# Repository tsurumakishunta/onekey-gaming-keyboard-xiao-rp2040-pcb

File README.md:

# OneKey Gaming Keyboard PCB for XIAO RP2040

[日本語](#日本語) | [English](#english)

## 日本語

### 概要

Seeed Studio XIAO RP2040とPCBマウント式の5ピンMXスイッチを上下に重ねる、1キーUSBゲーミングキーボード専用のKiCad基板設計です。

上側のキャリア基板をXIAO RP2040と同じ位置に重ね、XIAOに搭載されているRGB LEDの光軸をMXスイッチの光窓へ合わせます。キャリア基板に外付けLEDは搭載せず、XIAOの内蔵RGB LEDを利用します。

本プロジェクトでは基板の製造と実装まで行っています。ただし、部品メーカーや製造ロットによる寸法差があるため、再製造するときは後述の注意事項を確認し、最初に少数で試作してください。

### 専用ファームウェア

この基板は、次のファームウェアリポジトリと組み合わせて使用できます。

**[onekey-gaming-keyboard-xiao-rp2040](https://github.com/tsurumakishunta/onekey-gaming-keyboard-xiao-rp2040)**

専用ファームウェアを書き込むと、次のように動作します。

- MXスイッチを1回押すと、USBキーボード入力として `arigatou` を1回送信します。
- 日本語IMEがローマ字入力になっている場合、通常は「ありがとう」と入力されます。
- Enterキーは送信しません。
- XIAO RP2040の内蔵RGB LEDが、7色の滑らかなグラデーションで光り続けます。

この基板だけではUSBキーボードとして動作しません。XIAO RP2040へのファームウェア書き込みが必要です。

### 基板の構造

- 下側：部品面を上にしたSeeed Studio XIAO RP2040
- 上側：MXスイッチを取り付ける積層キャリア基板
- XIAO側：1列7ピンのメスソケットを2本
- キャリア基板側：1列7ピンのオスヘッダーを2本
- スイッチ：PCBマウント式の標準5ピンMX互換スイッチ
- USB-C端子：XIAO RP2040の端子をそのまま使用

不透明な下部ハウジングのMXスイッチでは、XIAOのRGB LEDの光がキーへ届きません。RGB対応の透明または半透明ハウジングを持つスイッチと、光を通すキーキャップを使用してください。

この設計はホットスワップソケットには対応しておらず、手はんだを前提としています。MX Low Profile、Kailh Choc、光学式、磁気式スイッチ用の基板ではありません。

### 回路

回路は、MXスイッチをXIAO RP2040のD0とGNDの間に接続するシンプルな構成です。

```text
XIAO pin 1  D0 / GPIO26 ---- SW1 pad 1
XIAO pin 13 GND ----------- SW1 pad 2
```

ファームウェアがXIAOの内部プルアップ抵抗を有効にするため、キャリア基板上に外付け抵抗、ダイオード、コンデンサー、LEDはありません。

ヘッダー穴とMXスイッチの接点穴はスルーホールメッキされています。MXスイッチの中央・左右の固定穴と、面付け基板のミシン目は非メッキ穴です。

### 単体基板の仕様

| 項目 | 仕様 |
|---|---:|
| リビジョン | Rev.B |
| 外形寸法 | 21.10 × 17.80 mm |
| 層数 | 2層 |
| 基板厚 | 1.00 mm |
| 材質 | FR-4 |
| 銅厚 | 1 oz想定 |
| 角 | R1.00 mm |
| MXスイッチ | PCBマウント式5ピン、1U |
| スイッチ入力 | D0 / GPIO26、押下時GND |

基板厚は、積層高さとMXスイッチの固定形状を考慮して **1.00 mm** を前提にしています。1.60 mmへ変更する場合は、ヘッダーのかみ合わせ、MXスイッチの固定爪、端子の突出量、XIAO上の部品との干渉を改めて確認してください。

### 4×5面付け基板

JLCPCBなどへまとめて発注できるように、単体基板を20枚配置したミシン目付きパネルを収録しています。

| 項目 | 仕様 |
|---|---:|
| 配列 | 4列 × 5行 |
| 取得できる単体基板 | 20枚 |
| パネル外形 | 98.40 × 95.40 mm |
| 単体基板ピッチ | 22.70 × 19.40 mm |
| ルーター溝 | 1.60 mm |
| 左右レール | 3.00 mm |
| タブ幅 | 5.00 mm |
| ミシン目 | 1列につき5穴、穴径0.60 mm、ピッチ0.95 mm |

部品を付けた状態で基板を折ると、スイッチ、ヘッダー、はんだ部へ大きな力がかかります。必ず基板を切り離し、端面を整えてから部品を実装してください。

### JLCPCB向け製造データ

アップロード用Gerber ZIPは次の場所にあります。

[`fabrication/onekey_revb_4x5_panel_JLCPCB.zip`](fabrication/onekey_revb_4x5_panel_JLCPCB.zip)

```text
SHA-256: E2092C8DA0B966CC4B055C34EE1AFF2BCEEBEC182B71E3D3F318ED53CC495E65
```

主な想定設定は次のとおりです。

- 2層、FR-4、1.00 mm、1 oz
- 面付け済み／Customer Panel
- 異なるデザイン数：1
- 4列 × 5行
- JLCPCBによる自動面付け：なし
- Vカット：なし
- PCBA：なし（自分ではんだ付け）

発注画面の名称や料金条件は変更される場合があります。アップロード後に検出寸法が **98.40 × 95.40 mm**、層数が2層であることを確認し、Gerberビューアで20枚すべての外形、光学ノッチ、配線、スルーホール、ミシン目を確認してください。面付けやルーター加工による追加料金が発生する可能性もあります。

### 組み立て時の注意

1. 4×5パネルを単体基板へ切り離し、ミシン目の端面を整えます。
2. キャリア基板の下面へオスヘッダーを取り付け、上面側ではんだ付けします。
3. 上面に残る端子がMXスイッチへ干渉しないよう、必要に応じて安全に処理します。
4. XIAO RP2040の部品面へメスソケットを取り付けます。
5. ヘッダーの向き、USB-C側、RGB LEDとMX光窓の位置を確認してからMXスイッチをはんだ付けします。
6. 導通と短絡がないことを確認してからXIAOを接続します。
7. 専用ファームウェアを書き込み、最初は空のテキストエディターで動作を確認します。

USBへ接続する前に、D0とGNDの短絡、隣接ヘッダーピン間のはんだブリッジ、XIAO上の部品とMX端子の接触がないことをテスターで確認してください。

### 検証と制限事項

- KiCad 10のERC：違反0件
- 単体基板のKiCad 10 DRC：違反0件、未接続0件
- 4×5パネルのKiCad 10 DRC：違反0件、未接続0件
- Gerber ZIP：銅箔2層、ソルダーマスク2層、シルク2層、外形、PTH・NPTHドリルを収録

ERCとDRCは、設計へ登録された電気的・二次元的な製造ルールを検査するものです。コネクターの実際の挿入深さ、基板間の高さ、MXスイッチ端子とXIAO部品のクリアランス、RGB光軸、キーキャップ、3Dプリントケースとの組み合わせまでは保証しません。使用する部品の現物で確認してください。

### KiCadで開く

KiCad 10以降で、次のプロジェクトファイルを開きます。

- 単体基板：[`hardware/revb_stacked/onekey_stacked_rev_b.kicad_pro`](hardware/revb_stacked/onekey_stacked_rev_b.kicad_pro)
- 4×5面付け：[`hardware/revb_panel/onekey_revb_4x5_panel.kicad_pro`](hardware/revb_panel/onekey_revb_4x5_panel.kicad_pro)

プロジェクト固有のシンボルとフットプリントは各ディレクトリの `libraries/` に含まれ、ライブラリテーブルは `${KIPRJMOD}` を使用した相対パスになっています。

### ファイル構成

```text
.
├── hardware/
│   ├── revb_stacked/       単体基板の回路図・PCB・プロジェクト内ライブラリ
│   └── revb_panel/         4×5面付けPCB・プロジェクト内ライブラリ
├── fabrication/            JLCPCBアップロード用Gerber ZIPとSHA-256
├── docs/images/            KiCadで生成した説明用レンダー
├── LICENSES/               第三者ライセンス
├── THIRD_PARTY_NOTICES.md  第三者データの出典と変更内容
├── LICENSE                 本プロジェクト独自部分のライセンス
└── README.md
```

### ライセンス

本プロジェクト独自部分はMIT Licenseです。プロジェクト内シンボルとフットプリントには、Seeed StudioおよびKiCad公式ライブラリを基に変更した部分が含まれます。詳細は [`THIRD_PARTY_NOTICES.md`](THIRD_PARTY_NOTICES.md) と `LICENSES/` を参照してください。

---

## English

### Overview

This repository contains the KiCad design files for a dedicated one-key USB gaming keyboard PCB. A PCB-mount five-pin MX switch is stacked directly above a standard Seeed Studio XIAO RP2040. The optical opening of the switch is aligned with the XIAO onboard addressable RGB LED, so no external LED is fitted to the carrier PCB.

The project has reached physical PCB fabrication and hand assembly. Component dimensions can still vary by manufacturer and production lot, so verify the actual switch, headers, sockets, keycap, and enclosure before ordering more than a small prototype quantity.

### Firmware

Use this PCB with the dedicated firmware repository:

**[onekey-gaming-keyboard-xiao-rp2040](https://github.com/tsurumakishunta/onekey-gaming-keyboard-xiao-rp2040)**

The firmware types `arigatou` once per press, does not send Enter, and continuously animates the XIAO onboard RGB LED through a smooth seven-color gradient. With a Japanese IME in romaji mode, the typed text will usually appear as `ありがとう`. The PCB does not operate as a USB keyboard until firmware has been installed on the XIAO RP2040.

### Electrical design

```text
XIAO pin 1  D0 / GPIO26 ---- SW1 pad 1
XIAO pin 13 GND ----------- SW1 pad 2
```

The firmware enables the internal pull-up. The carrier has no external resistor, diode, capacitor, or LED.

### Board specifications

- Single carrier: 21.10 × 17.80 mm, two-layer FR-4, 1.00 mm finished thickness
- Switch: PCB-mount five-pin 1U MX-compatible switch with a translucent RGB-capable lower housing
- Panel: 4 × 5 array, 20 boards, 98.40 × 95.40 mm
- Routed gaps: 1.60 mm; side rails: 3.00 mm; breakaway tabs: 5.00 mm
- Mouse bites: five 0.60 mm NPTH holes per row at 0.95 mm pitch
- Assembly: hand soldering after depanelization; hot-swap sockets are not supported

### JLCPCB fabrication package

The upload-ready Gerber archive is [`fabrication/onekey_revb_4x5_panel_JLCPCB.zip`](fabrication/onekey_revb_4x5_panel_JLCPCB.zip).

```text
SHA-256: E2092C8DA0B966CC4B055C34EE1AFF2BCEEBEC182B71E3D3F318ED53CC495E65
```

The intended baseline is a two-layer, 1.00 mm FR-4, 1 oz, customer-panelized PCB with one identical design arranged in four columns and five rows. Do not request automatic panelization, V-cuts, or PCBA. Verify the detected 98.40 × 95.40 mm dimensions and inspect every layer and drill file in the online Gerber viewer before ordering. Service labels, capabilities, and prices may change.

### Validation and limitations

KiCad 10 ERC and DRC pass with zero violations for the single-board project, and panel DRC passes with zero violations and zero unconnected pads. These checks validate only the encoded electrical and two-dimensional manufacturing rules. They do not guarantee connector insertion depth, board-to-board height, clearance to XIAO components, the optical path through a particular MX switch, keycap fit, or enclosure fit. Verify those items with the exact physical parts you intend to use.

Open the single-board project at [`hardware/revb_stacked/onekey_stacked_rev_b.kicad_pro`](hardware/revb_stacked/onekey_stacked_rev_b.kicad_pro) or the panel project at [`hardware/revb_panel/onekey_revb_4x5_panel.kicad_pro`](hardware/revb_panel/onekey_revb_4x5_panel.kicad_pro) using KiCad 10 or later.

### License

Original project material is released under the MIT License. Some project-local symbols and footprints contain modified material based on the Seeed Studio and official KiCad libraries. See [`THIRD_PARTY_NOTICES.md`](THIRD_PARTY_NOTICES.md) and `LICENSES/` for their source and license terms.

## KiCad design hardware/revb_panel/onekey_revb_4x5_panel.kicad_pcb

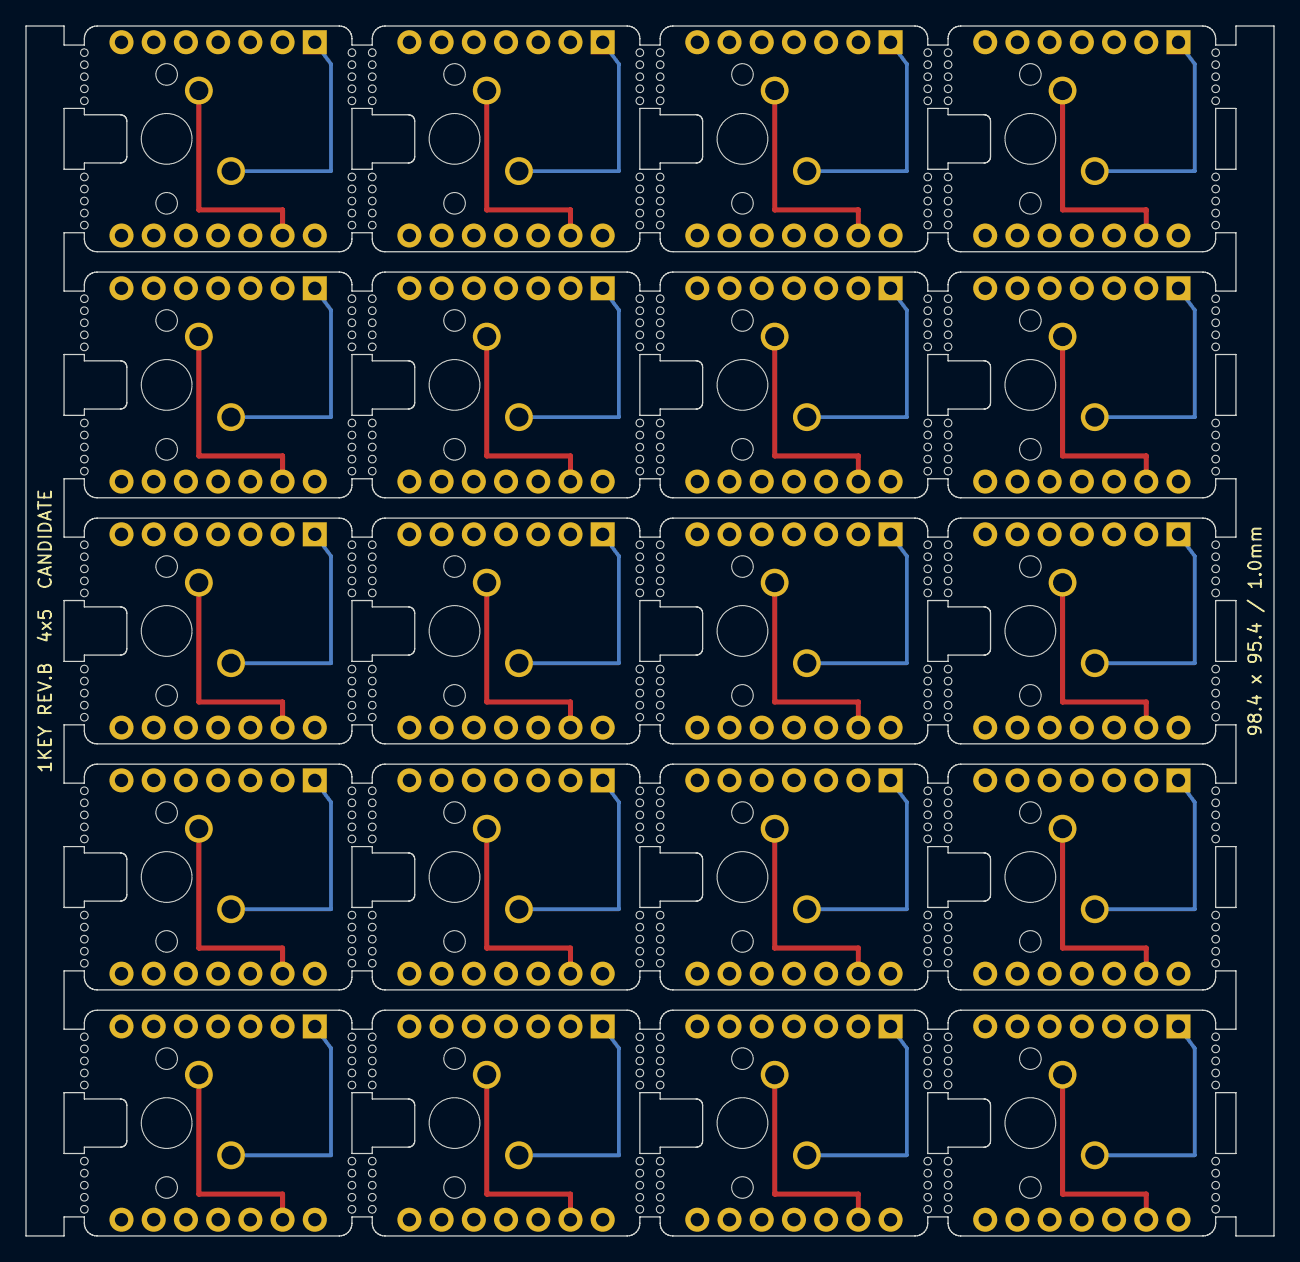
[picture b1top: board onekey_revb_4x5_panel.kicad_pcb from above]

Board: 2 copper layers, 98.4 x 95.4 mm, 120 parts (0 on the bottom side), 40 nets.

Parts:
MB001, MB002, MB003, MB004, MB005, MB006, MB007, MB008, MB009, MB010, MB011, MB012, MB013, MB014, MB015, MB016, MB017, MB018, MB019, MB020, MB021, MB022, MB023, MB024, MB025, MB026, MB027, MB028, MB029, MB030, MB031, MB032, MB033, MB034, MB035, MB036, MB037, MB038, MB039, MB040, MB041, MB042, MB043, MB044, MB045, MB046, MB047, MB048, MB049, MB050, MB051, MB052, MB053, MB054, MB055, MB056, MB057, MB058, MB059, MB060, MB061, MB062, MB063, MB064, MB065, MB066, MB067, MB068, MB069, MB070, MB071, MB072, MB073, MB074, MB075, MB076, MB077, MB078, MB079, MB080: MouseBite_5x0.60_P0.95
SW01, SW02, SW03, SW04, SW05, SW06, SW07, SW08, SW09, SW10, SW11, SW12, SW13, SW14, SW15, SW16, SW17, SW18, SW19, SW20: CHERRY MX2A RGB 5-pin; SW_Cherry_MX_1.00u_PCB_RGB_Panel
U01, U02, U03, U04, U05, U06, U07, U08, U09, U10, U11, U12, U13, U14, U15, U16, U17, U18, U19, U20: 2x 1x7 MALE / FH SOCKET BELOW; XIAO_RP2040_Upper_Header_Interface_Panel

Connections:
GND_B01: SW01.2, U01.13 (GND)
GND_B02: SW02.2, U02.13 (GND)
GND_B03: SW03.2, U03.13 (GND)
GND_B04: SW04.2, U04.13 (GND)
GND_B05: SW05.2, U05.13 (GND)
GND_B06: SW06.2, U06.13 (GND)
GND_B07: SW07.2, U07.13 (GND)
GND_B08: SW08.2, U08.13 (GND)
GND_B09: SW09.2, U09.13 (GND)
GND_B10: SW10.2, U10.13 (GND)
GND_B11: SW11.2, U11.13 (GND)
GND_B12: SW12.2, U12.13 (GND)
GND_B13: SW13.2, U13.13 (GND)
GND_B14: SW14.2, U14.13 (GND)
GND_B15: SW15.2, U15.13 (GND)
GND_B16: SW16.2, U16.13 (GND)
GND_B17: SW17.2, U17.13 (GND)
GND_B18: SW18.2, U18.13 (GND)
GND_B19: SW19.2, U19.13 (GND)
GND_B20: SW20.2, U20.13 (GND)
KEY_D0_B01: SW01.1, U01.1 (D0/GPIO26)
KEY_D0_B02: SW02.1, U02.1 (D0/GPIO26)
KEY_D0_B03: SW03.1, U03.1 (D0/GPIO26)
KEY_D0_B04: SW04.1, U04.1 (D0/GPIO26)
KEY_D0_B05: SW05.1, U05.1 (D0/GPIO26)
KEY_D0_B06: SW06.1, U06.1 (D0/GPIO26)
KEY_D0_B07: SW07.1, U07.1 (D0/GPIO26)
KEY_D0_B08: SW08.1, U08.1 (D0/GPIO26)
KEY_D0_B09: SW09.1, U09.1 (D0/GPIO26)
KEY_D0_B10: SW10.1, U10.1 (D0/GPIO26)
KEY_D0_B11: SW11.1, U11.1 (D0/GPIO26)
KEY_D0_B12: SW12.1, U12.1 (D0/GPIO26)
KEY_D0_B13: SW13.1, U13.1 (D0/GPIO26)
KEY_D0_B14: SW14.1, U14.1 (D0/GPIO26)
KEY_D0_B15: SW15.1, U15.1 (D0/GPIO26)
KEY_D0_B16: SW16.1, U16.1 (D0/GPIO26)
KEY_D0_B17: SW17.1, U17.1 (D0/GPIO26)
KEY_D0_B18: SW18.1, U18.1 (D0/GPIO26)
KEY_D0_B19: SW19.1, U19.1 (D0/GPIO26)
KEY_D0_B20: SW20.1, U20.1 (D0/GPIO26)
